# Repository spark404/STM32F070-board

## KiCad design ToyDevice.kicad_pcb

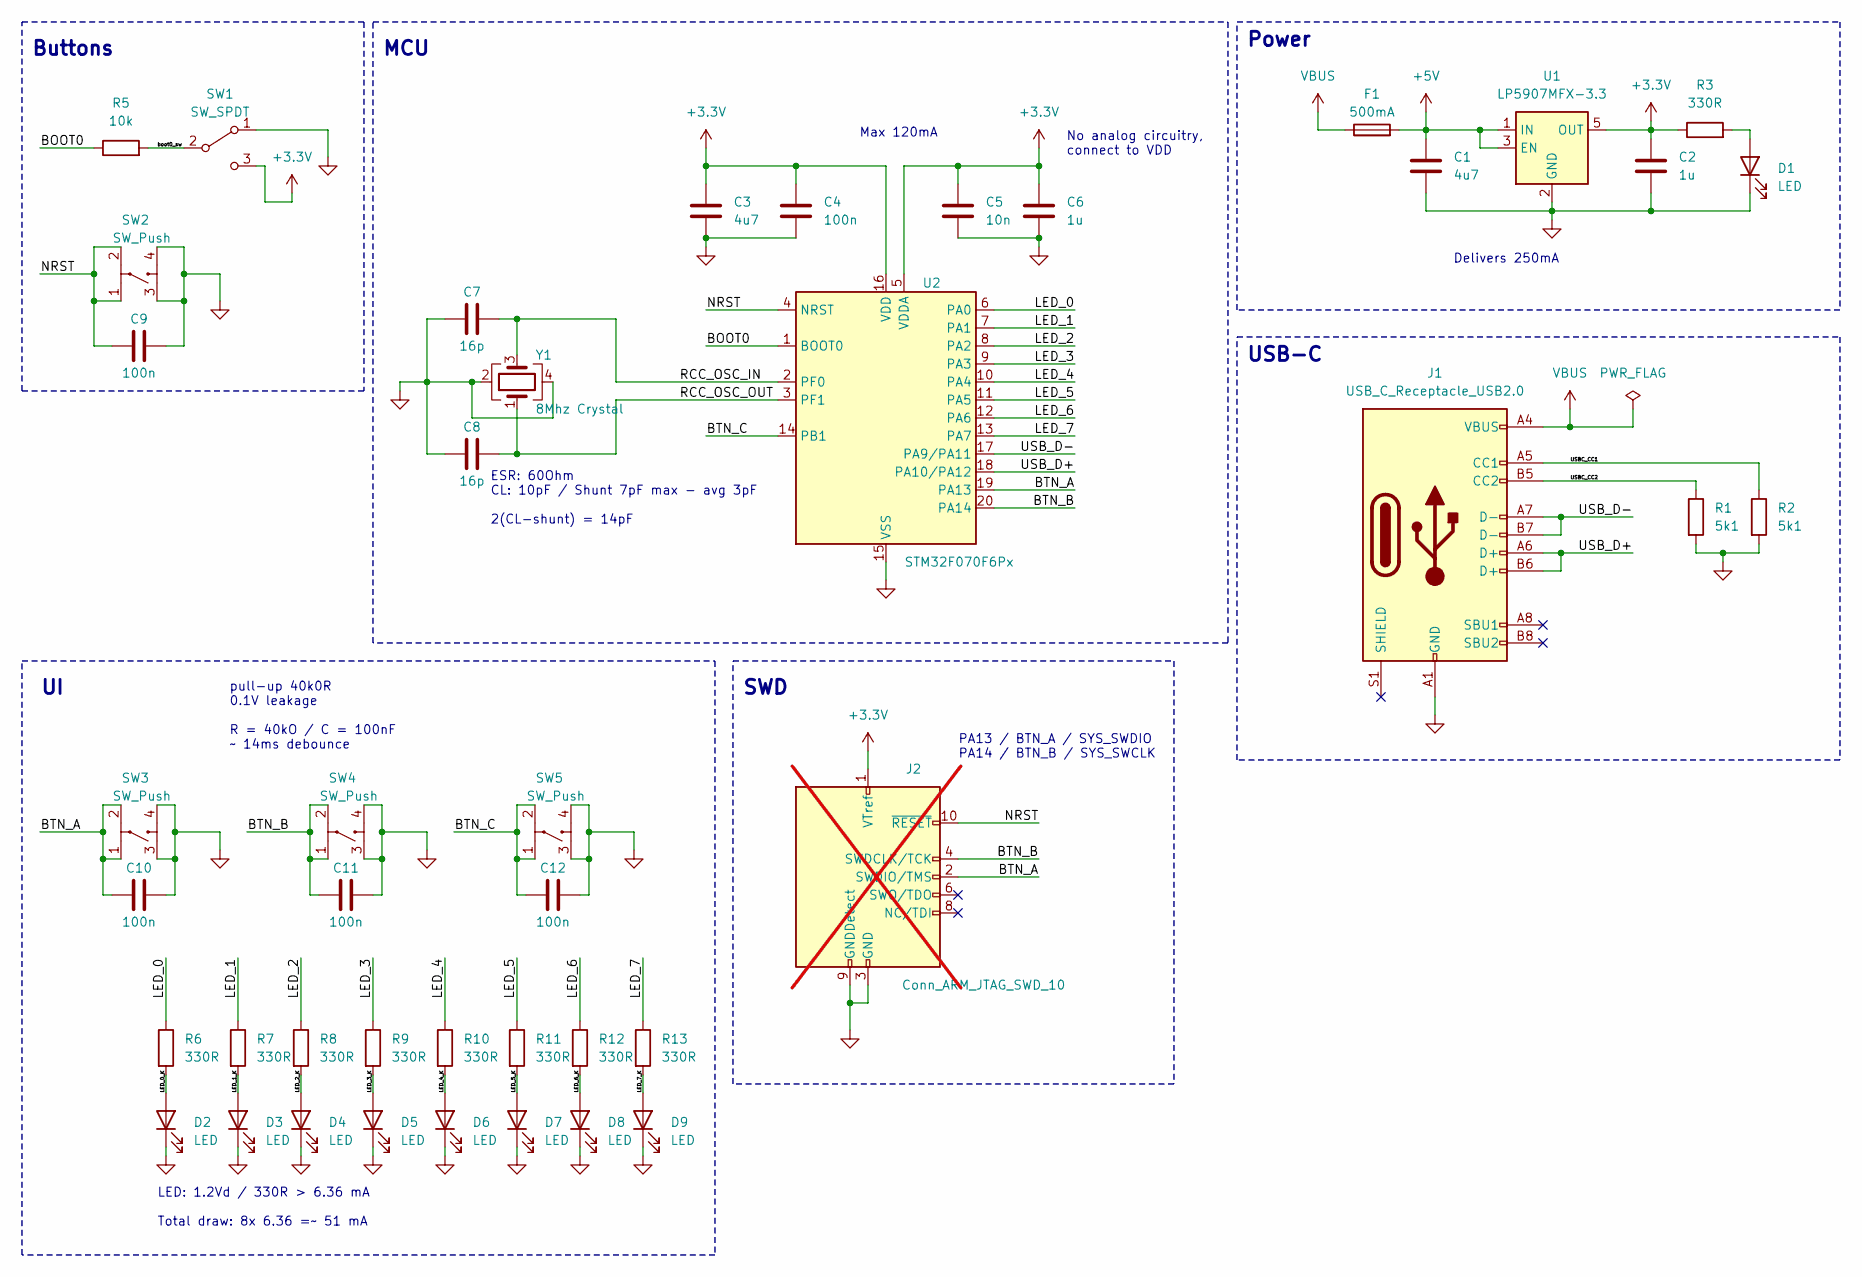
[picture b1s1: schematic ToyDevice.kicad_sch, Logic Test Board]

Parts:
C1, C3: 4u7; C_0402_1005Metric; Mfr Part 0402X475K6R3CT; LCSC C5173643
C2, C6: 1u; C_0402_1005Metric; Mfr Part GRM155R70J105MA12D; LCSC C913490
C4, C9, C10, C11, C12: 100n; C_0402_1005Metric; Mfr Part CL05A105KQ5NNNC; LCSC C107372
C5: 10n; C_0402_1005Metric; Mfr Part GRM1555CYA103JE01D; LCSC C1518210
C7, C8: 16p; C_0402_1005Metric; Mfr Part CC0402GRNPO9BN160; LCSC C513591
D1, D2, D3, D4, D5, D6, D7, D8, D9: LED; LED_0603_1608Metric; Mfr Part 19-213/Y2C-CQ2R2L/3T(CY); LCSC C72038
F1: 500mA; Fuse_0402_1005Metric; Mfr Part JFC0402-0500FS; LCSC C136320
J1: USB_C_Receptacle_USB2.0; SHOU-HAN-TYPE-C-16PFS-2J-H7-45-IPX8; Mfr Part TYPE-C 16PFS 2J-H7.45 IPX8; LCSC C3020050
J2: Conn_ARM_JTAG_SWD_10; PinHeader_2x05_P1.27mm_Vertical; not fitted
R1, R2: 5k1; R_0402_1005Metric; Mfr Part PTFR0402B5K11P9; LCSC C2692894
R3, R6, R7, R8, R9, R10, R11, R12, R13: 330R; R_0402_1005Metric; Mfr Part RAT023300FTH; LCSC C5139567
R5: 10k; R_0402_1005Metric; Mfr Part MCR01MZPJ103; LCSC C308028
SW1: SW_SPDT; MK-12C02-G025; Mfr Part MK-12C02-G025; LCSC C778186
SW2, SW3, SW4, SW5: SW_Push; XKB_TS_1187A_X_X_X; Mfr Part TS-1187A-B-A-B; LCSC C318884
U1: LP5907MFX-3.3; SOT-23-5; Mfr Part LP5907MFX-3.3/NOPB; LCSC C80670
U2: STM32F070F6Px; TSSOP-20_4.4x6.5mm_P0.65mm; Mfr Part STM32F070F6P6; LCSC C86951
Y1: 8Mhz Crystal; Crystal_SMD_3225-4Pin_3.2x2.5mm; Mfr Part S32080001010500; LCSC C479191

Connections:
+3.3V: C2.1, C3.1, C4.1, C5.1, C6.1, J2.1 (VTref), R3.1, SW1.3 (C), U1.5 (OUT), U2.5 (VDDA), U2.16 (VDD)
+5V: C1.1, F1.2, U1.1 (IN), U1.3 (EN)
/BOOT0: R5.1, U2.1 (BOOT0)
/BTN_A: C10.2, J2.2 (SWDIO/TMS), SW3.1, SW3.2, U2.19 (PA13)
/BTN_B: C11.2, J2.4 (SWDCLK/TCK), SW4.1, SW4.2, U2.20 (PA14)
/BTN_C: C12.2, SW5.1, SW5.2, U2.14 (PB1)
/LED_0: R6.1, U2.6 (PA0)
/LED_0_K: D2.2 (A), R6.2
/LED_1: R7.1, U2.7 (PA1)
/LED_1_K: D3.2 (A), R7.2
/LED_2: R8.1, U2.8 (PA2)
/LED_2_K: D4.2 (A), R8.2
/LED_3: R9.1, U2.9 (PA3)
/LED_3_K: D5.2 (A), R9.2
/LED_4: R10.1, U2.10 (PA4)
/LED_4_K: D6.2 (A), R10.2
/LED_5: R11.1, U2.11 (PA5)
/LED_5_K: D7.2 (A), R11.2
/LED_6: R12.1, U2.12 (PA6)
/LED_6_K: D8.2 (A), R12.2
/LED_7: R13.1, U2.13 (PA7)
/LED_7_K: D9.2 (A), R13.2
/NRST: C9.2, J2.10 (~RESET), SW2.1, SW2.2, U2.4 (NRST)
/RCC_OSC_IN: C7.2, U2.2 (PF0), Y1.3
/RCC_OSC_OUT: C8.2, U2.3 (PF1), Y1.1
/USBC_CC1: J1.A5 (CC1), R2.1
/USBC_CC2: J1.B5 (CC2), R1.1
/USB_D+: J1.A6 (D+), J1.B6 (D+), U2.18 (PA10/PA12)
/USB_D-: J1.A7 (D-), J1.B7 (D-), U2.17 (PA9/PA11)
/boot0_sw: R5.2, SW1.2 (B)
GND: C1.2, C2.2, C3.2, C4.2, C5.2, C6.2, C7.1, C8.1, C9.1, C10.1, C11.1, C12.1, D1.1 (K), D2.1 (K), D3.1 (K), D4.1 (K), D5.1 (K), D6.1 (K), D7.1 (K), D8.1 (K), D9.1 (K), J1.A1 (GND), J1.A12 (GND), J1.B1 (GND), J1.B12 (GND), J2.3 (GND), J2.5 (GND), J2.9 (GNDDetect), R1.2, R2.2, SW1.1 (A), SW2.3, SW2.4, SW3.3, SW3.4, SW4.3, SW4.4, SW5.3, SW5.4, U1.2 (GND), U2.15 (VSS), Y1.2, Y1.4
unnamed: D1.2 (A), R3.2
VBUS: F1.1, J1.A4 (VBUS), J1.A9 (VBUS), J1.B4 (VBUS), J1.B9 (VBUS)

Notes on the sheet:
MCU
PA13 / BTN_A / SYS_SWDIO PA14 / BTN_B / SYS_SWCLK
ESR: 60Ohm CL: 10pF / Shunt 7pF max - avg 3pF 2(CL-shunt) = 14pF
SWD
Power
LED: 1.2Vd / 330R > 6.36 mA Total draw: 8x 6.36 =~ 51 mA
Delivers 250mA
Buttons
No analog circuitry, connect to VDD
pull-up 40k0R 0.1V leakage R = 40kO / C = 100nF ~ 14ms debounce
USB-C
Max 120mA

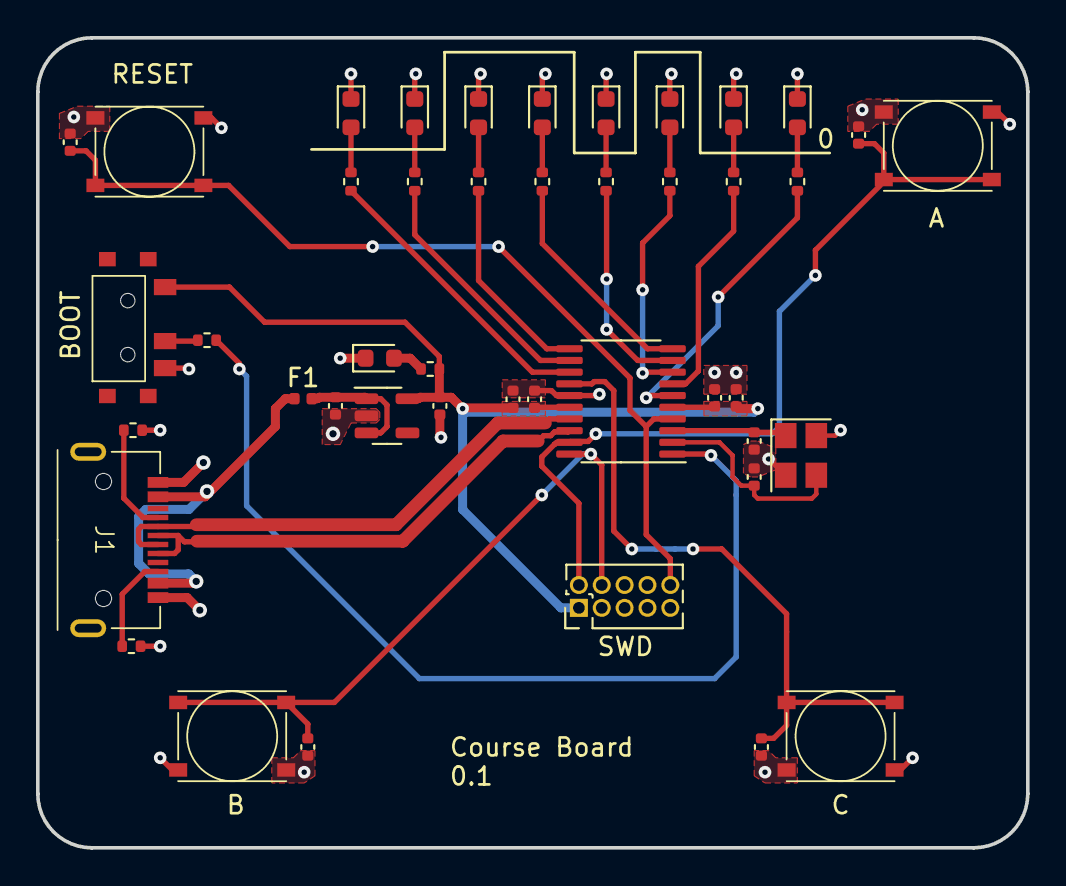
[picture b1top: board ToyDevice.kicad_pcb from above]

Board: 2 copper layers, 55.0 x 45.0 mm, 44 parts (0 on the bottom side), 33 nets.

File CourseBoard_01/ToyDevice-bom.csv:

Comment,Designator,Footprint,LCSC
"4u7","C1,C3","Capacitor_SMD:C_0402_1005Metric","C5173643"
"1u","C2,C6","Capacitor_SMD:C_0402_1005Metric","C913490"
"100n","C4,C9,C10,C11,C12","Capacitor_SMD:C_0402_1005Metric","C107372"
"10n","C5","Capacitor_SMD:C_0402_1005Metric","C1518210"
"16p","C7,C8","Capacitor_SMD:C_0402_1005Metric","C513591"
"LED","D1,D2,D3,D4,D5,D6,D7,D8,D9","LED_SMD:LED_0603_1608Metric","C72038"
"500mA","F1","Fuse:Fuse_0402_1005Metric","C136320"
"USB_C_Receptacle_USB2.0","J1","Hugo_Custom:SHOU-HAN-TYPE-C-16PFS-2J-H7-45-IPX8","C3020050"
"5k1","R1,R2","Resistor_SMD:R_0402_1005Metric","C2692894"
"330R","R3,R6,R7,R8,R9,R10,R11,R12,R13","Resistor_SMD:R_0402_1005Metric","C5139567"
"10k","R5","Resistor_SMD:R_0402_1005Metric","C308028"
"SW_SPDT","SW1","Hugo_Custom:MK-12C02-G025","C778186"
"SW_Push","SW2,SW3,SW4,SW5","Hugo_Custom:XKB_TS_1187A_X_X_X","C318884"
"LP5907MFX-3.3","U1","Package_TO_SOT_SMD:SOT-23-5","C80670"
"STM32F070F6Px","U2","Package_SO:TSSOP-20_4.4x6.5mm_P0.65mm","C86951"
"8Mhz Crystal","Y1","Crystal:Crystal_SMD_3225-4Pin_3.2x2.5mm","C479191"

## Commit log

2023-11-03 Course Board 0.1
2023-11-03 Add all part number
2023-11-04 Changed USB-C connector
2023-11-04 Change crystal capacitor to available type
2023-11-04 Add fabrication files for revision 0.1
2023-11-04 Fix missing connection RCC_OSC_OUT
2023-11-18 Cleanup the origin
